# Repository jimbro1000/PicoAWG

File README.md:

# Pi Pico AWG

The repository contains the design for a PCB to host
a Raspberry Pi Pico acting as an arbitrary wave
form generator

## Design

This is a prototype design.

The PCB is not optimised for size and the DAC can
be reduced to a single component. Optimisation of
the design could reduce the size of the board
substantially. The Pico device can be swapped out
for a smaller design than the official Pico
provided the exposed GPIO pins meet the requirements
of the AWG code (8 sequentially numbered IO pins).

## Software

The python code included is not my own and has been
taken from an instructables page by rgco 
https://www.instructables.com/Arbitrary-Wave-Generator-With-the-Raspberry-Pi-Pic/

## Usage

The pico must be operating with micropython installed
as a base requisite.

By default the pico requires a computer host to upload
and run the required python code. This is a minimally
interactive process and requires the user to hard code
the desired frequency and wave form.

The python code generates a set of digital samples (from
4096 samples up to 65536 samples). Once generated the pico
will automatically replay the sample on loop.

If the code is renamed as "main.py" and uploaded to the
pico it will automatically run that code on boot allowing
the board to be integrated with another system.

## Issues

The RUN button is currently ineffective, this was
tested on breadboard but does not appear to be
operating. It is also worth noting that contrary
to the software notes it actually behaves as a 
HALT operation intead of RUN.

In order to achieve reasonable accuracy the 
generated wave form requires a high sample size to
avoid jitter. Generating larger sample sizes increases
the time required to begin producing the wave form
output.

The micropython firmware and supplied python code 
currently have a problem working on the Pico 2. This
has been previously tested as working and the cause
of the fault is not yet known.

## License

This design is licensed under the Creative Commons
CC-BY-SA 4.0 International license 
https://creativecommons.org/licenses/by-sa/4.0/deed.en

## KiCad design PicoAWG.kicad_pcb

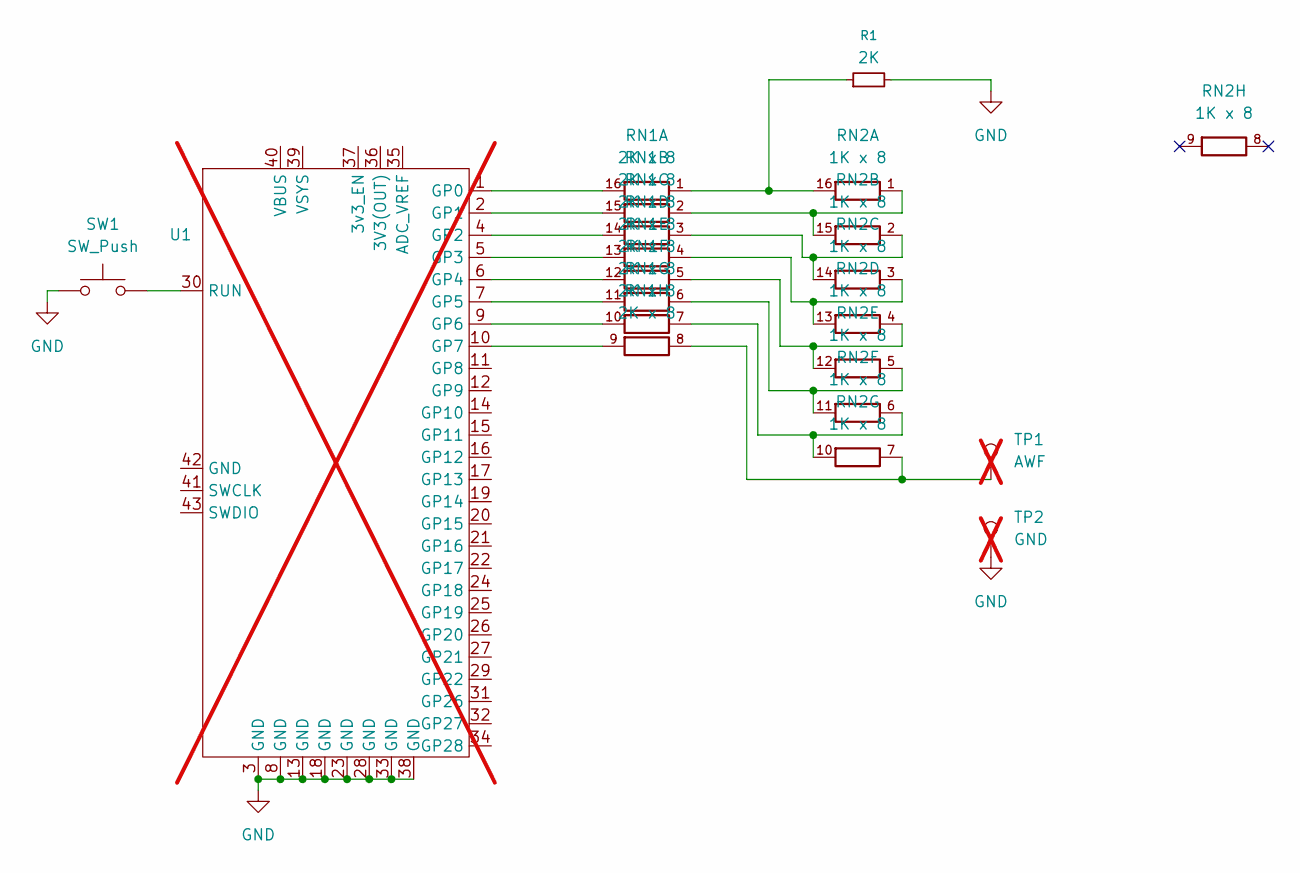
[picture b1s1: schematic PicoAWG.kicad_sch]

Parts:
R1: 2K; R_0603_1608Metric; LCSC C22975
RN1: 2K x 8; R_Array_Convex_8x0602; LCSC C422185
RN2: 1K x 8; R_Array_Convex_8x0602; LCSC C874604
SW1: SW_Push; SW_SPST_EVQP0; LCSC C3000008
TP1: AWF; TestPoint_Loop_D2.60mm_Drill1.6mm_Beaded; not fitted
TP2: GND; TestPoint_Loop_D2.60mm_Drill1.6mm_Beaded; not fitted
U1: RPi_Pico_SMD_TH; not fitted

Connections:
GND: R1.2, SW1.1, TP2.1, U1.3 (GND), U1.8 (GND), U1.13 (GND), U1.18 (GND), U1.23 (GND), U1.28 (GND), U1.33 (GND), U1.38 (GND)
unnamed: R1.1, RN1.1 (R1.1), RN2.16 (R1.2)
unnamed: RN1.16 (R1.2), U1.1 (GP0)
unnamed: RN1.2 (R2.1), RN2.1 (R1.1), RN2.15 (R2.2)
unnamed: RN1.15 (R2.2), U1.2 (GP1)
unnamed: RN1.3 (R3.1), RN2.2 (R2.1), RN2.14 (R3.2)
unnamed: RN1.14 (R3.2), U1.4 (GP2)
unnamed: RN1.4 (R4.1), RN2.3 (R3.1), RN2.13 (R4.2)
unnamed: RN1.13 (R4.2), U1.5 (GP3)
unnamed: RN1.5 (R5.1), RN2.4 (R4.1), RN2.12 (R5.2)
unnamed: RN1.12 (R5.2), U1.6 (GP4)
unnamed: RN1.6 (R6.1), RN2.5 (R5.1), RN2.11 (R6.2)
unnamed: RN1.11 (R6.2), U1.7 (GP5)
unnamed: RN1.7 (R7.1), RN2.6 (R6.1), RN2.10 (R7.2)
unnamed: RN1.10 (R7.2), U1.9 (GP6)
unnamed: RN1.8 (R8.1), RN2.7 (R7.1), TP1.1
unnamed: RN1.9 (R8.2), U1.10 (GP7)
unnamed: SW1.2, U1.30 (RUN)

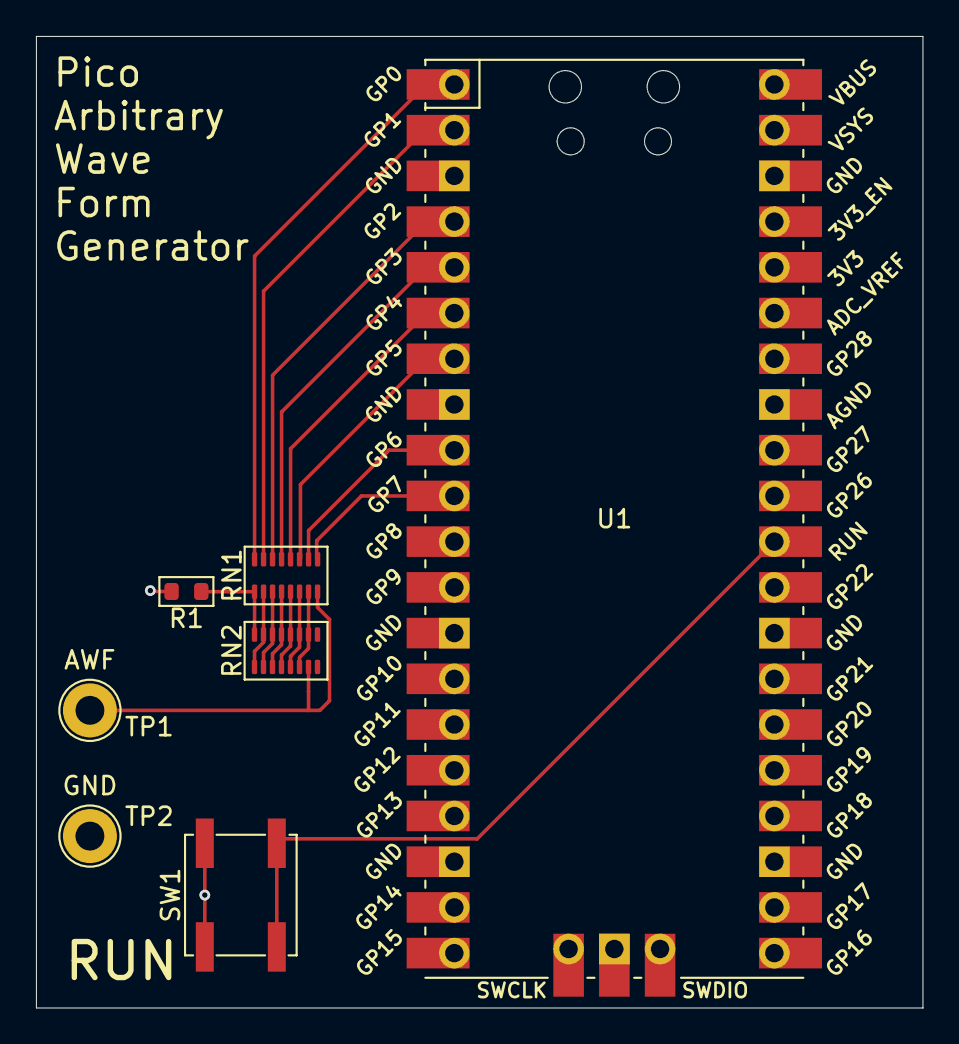
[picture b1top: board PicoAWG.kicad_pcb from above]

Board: 2 copper layers, 49.3 x 54.0 mm, 7 parts (0 on the bottom side), 18 nets.

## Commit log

2025-09-09 add readme and license
